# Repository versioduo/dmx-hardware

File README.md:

# dmx-hardware

🚥 MIDI to DMX Bridge

## Board

## Schematic

[PDF](dmx.pdf)

## Bill Of Materials

[Interactive BOM](https://htmlpreview.github.io/?https://github.com/versioduo/dmx-hardware/main/dmx-bom.html)

## Software

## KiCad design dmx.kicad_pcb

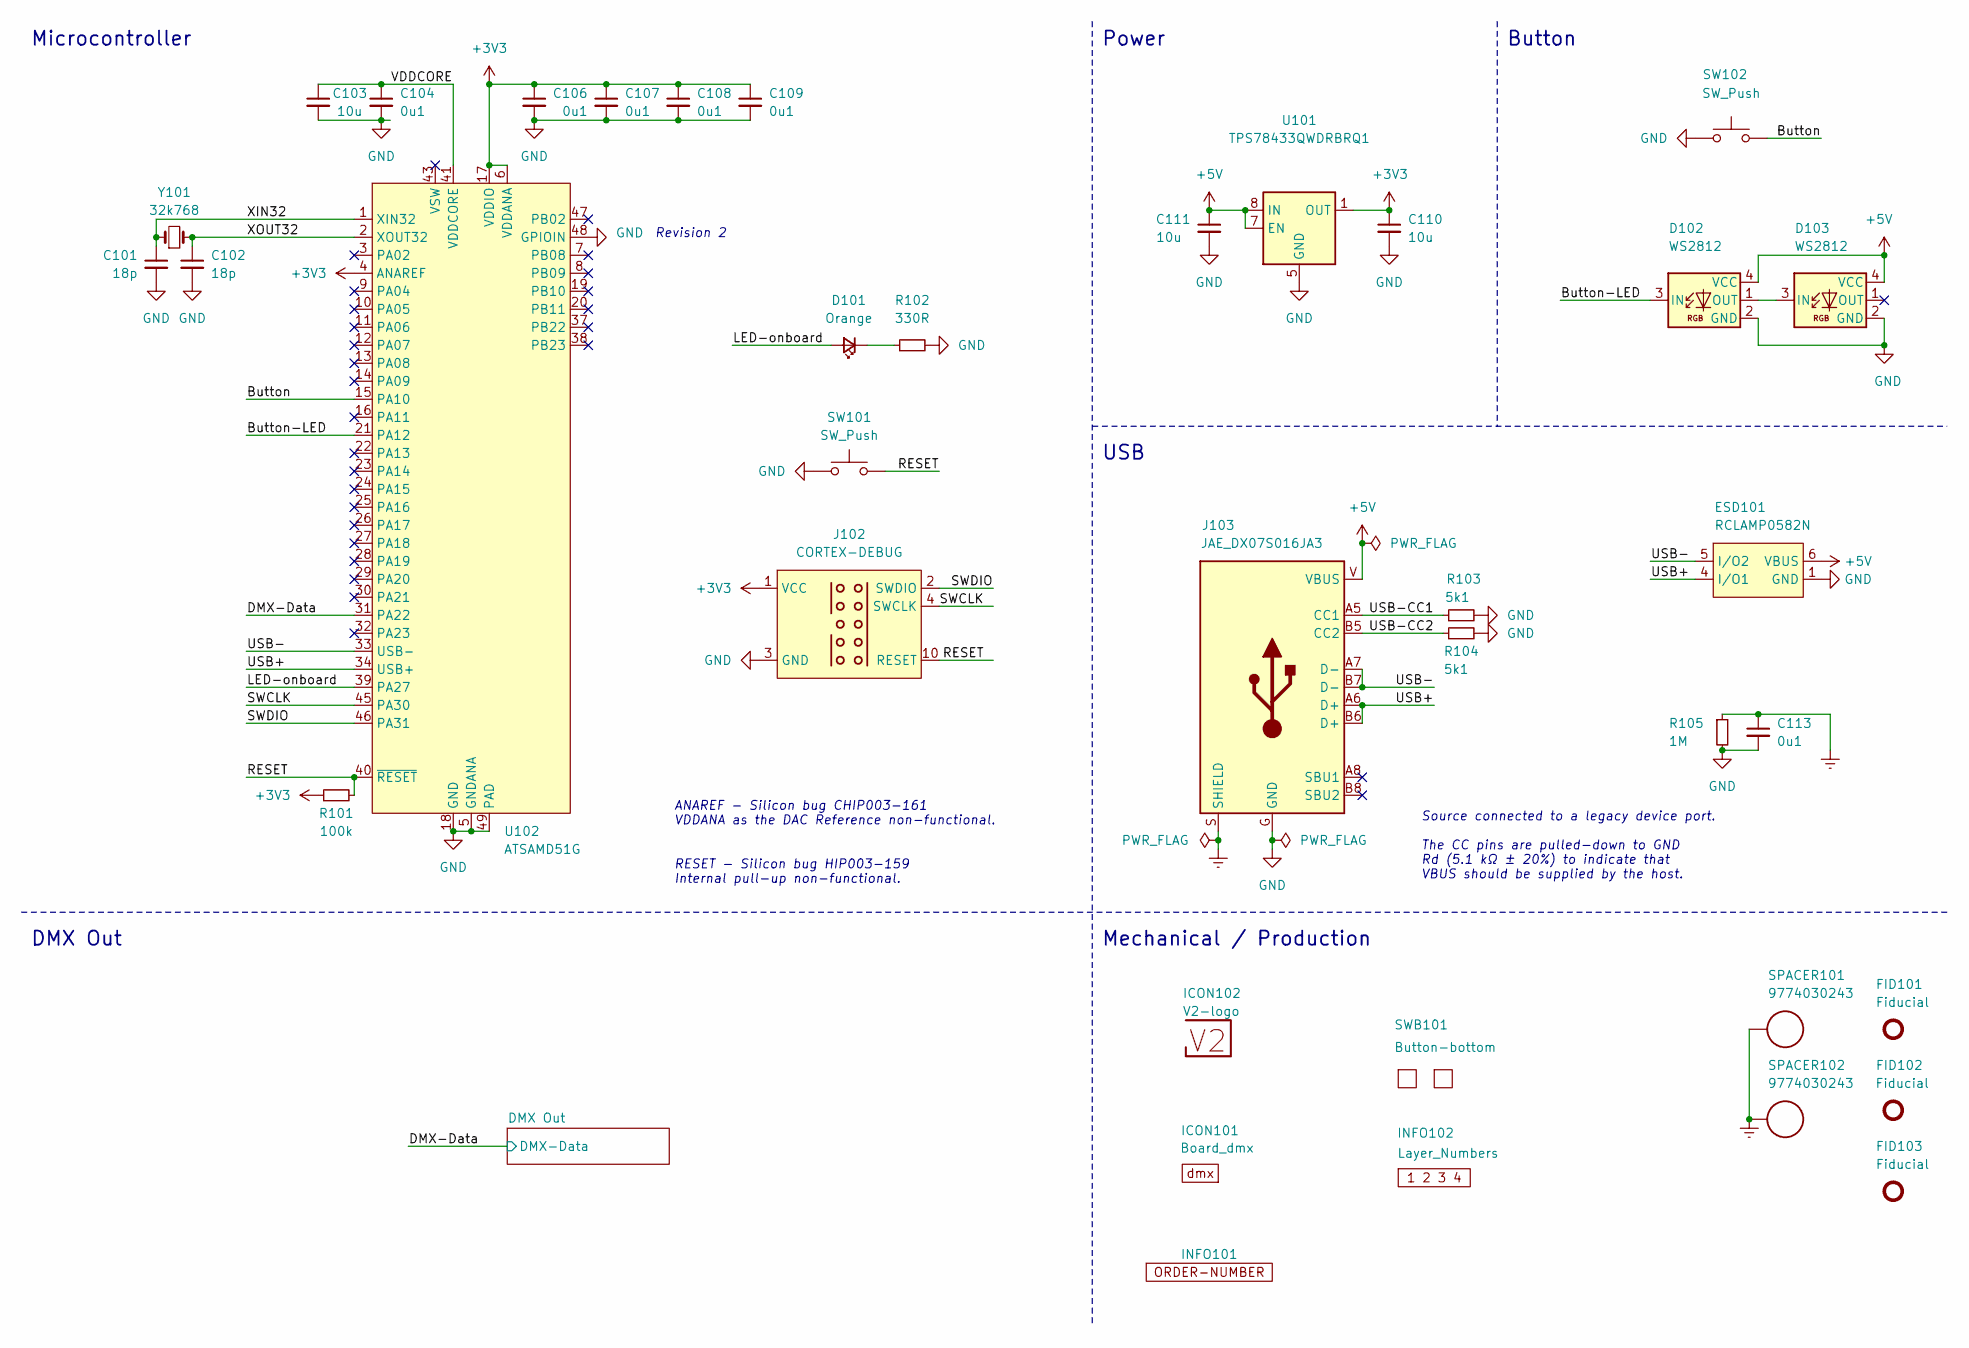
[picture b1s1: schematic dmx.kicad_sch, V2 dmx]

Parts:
C101, C102: 18p; C_0603_1608Metric
C103, C110, C111: 10u; C_0603_1608Metric
C104, C106, C107, C108, C109, C113: 0u1; C_0603_1608Metric
D101: Orange; LED_0603_1608Metric
D102, D103: WS2812; WS2812-2020
ESD101: RCLAMP0582N; SLP1210N6
FID101, FID102, FID103: Fiducial; Fiducial_0.5mm_Mask1mm_Paste
ICON101: Board_dmx; Board_dmx_Small
ICON102: V2-logo; Logo_Small
INFO101: ORDER-NUMBER; Order_Number
INFO102: Layer_Numbers
J102: CORTEX-DEBUG; Cortex_Debug_Pad
J103: JAE_DX07S016JA3
R101: 100k; R_0603_1608Metric
R102: 330R; R_0603_1608Metric
R103, R104: 5k1; R_0603_1608Metric
R105: 1M; R_0603_1608Metric
SPACER101, SPACER102: 9774030243
SW101, SW102: SW_Push; SKSG
SWB101: Button-bottom; PCB_Button-bottom
U101: TPS78433QWDRBRQ1; VSON-8-1_3x3mm_P0.65_EP1.65x2.4mm
U102: ATSAMD51G; QFN-48-1EP_7x7mm_P0.5mm_EP5.45x5.45mm_ThermalVias
Y101: 32k768; Crystal_SMD_3215-2Pin_3.2x1.5mm

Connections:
+3V3: C106.1, C107.1, C108.1, C109.1, C110.1, J102.1 (VCC), R101.1, U101.1 (OUT), U102.4 (ANAREF), U102.6 (VDDANA), U102.17 (VDDIO), U102.36 (VDDIO), U102.44 (VDDIO); also elsewhere on the board
+5V: C111.1, D102.4 (VCC), D103.4 (VCC), ESD101.6 (VBUS), J103.V (VBUS), U101.7 (EN), U101.8 (IN)
/Button: SW102.2, U102.15 (PA10)
/Button-LED: D102.3 (IN), U102.21 (PA12)
/DMX-Data: U102.31 (PA22); also elsewhere on the board
/LED-onboard: D101.2 (A), U102.39 (PA27)
/RESET: J102.10 (RESET), R101.2, SW101.2, U102.40 (~RESET)
/SWCLK: J102.4 (SWCLK), U102.45 (PA30)
/SWDIO: J102.2 (SWDIO), U102.46 (PA31)
/USB+: ESD101.4 (I/O1), J103.A6 (D+), J103.B6 (D+), U102.34 (USB+)
/USB-: ESD101.5 (I/O2), J103.A7 (D-), J103.B7 (D-), U102.33 (USB-)
/USB-CC1: J103.A5 (CC1), R103.1
/USB-CC2: J103.B5 (CC2), R104.1
/VDDCORE: C103.1, C104.1, U102.41 (VDDCORE)
/XIN32: C101.1, U102.1 (XIN32), Y101.1
/XOUT32: C102.1, U102.2 (XOUT32), Y101.2
Earth: C113.1, J103.S (SHIELD), R105.1, SPACER101.1, SPACER102.1
GND: C101.2, C102.2, C103.2, C104.2, C106.2, C107.2, C108.2, C109.2, C110.2, C111.2, C113.2, D102.2 (GND), D103.2 (GND), ESD101.1 (GND), J102.3 (GND), J102.5 (GND), J103.G (GND), R102.2, R103.2, R104.2, R105.2, SW101.1, SW102.1, U101.5 (GND), U101.9 (GND), U102.5 (GNDANA), U102.18 (GND), U102.35 (GND), U102.42 (GND), U102.48 (GPIOIN), U102.49 (PAD); also elsewhere on the board
unnamed: D101.1 (K), R102.1
unnamed: D102.1 (OUT), D103.3 (IN)

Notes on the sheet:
﻿ANAREF - Silicon bug CHIP003-161 VDDANA as the DAC Reference non-functional.
RESET - ﻿Silicon bug HIP003-159 Internal pull-up non-functional.
﻿Source connected to a legacy device port. The CC pins are pulled-down to GND Rd (5.1 kΩ ± 20%) to indicate that VBUS should be supplied by the host.
Button
Revision 2
Mechanical / Production
Power
Microcontroller
USB
DMX Out

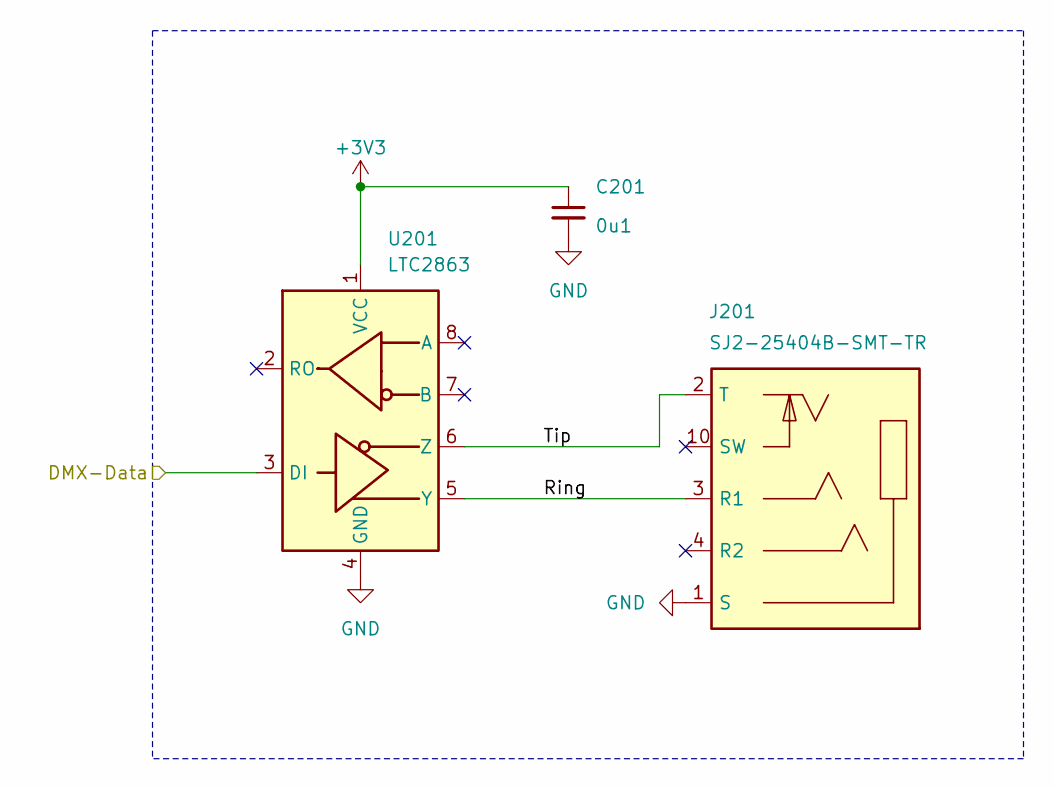
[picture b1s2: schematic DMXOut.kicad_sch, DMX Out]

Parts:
C201: 0u1; C_0603_1608Metric
J201: SJ2-25404B-SMT-TR; CUI_SJ2-25404B-SMT-TR
U201: LTC2863; DFN-8-1EP_3x3mm_P0.5mm_EP1.65x2.38mm

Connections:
+3V3: C201.1, U201.1 (VCC); also elsewhere on the board
/DMX Out/Ring: J201.3 (R1), U201.5 (Y)
/DMX Out/Tip: J201.2 (T), U201.6 (Z)
/DMX-Data: U201.3 (DI); also elsewhere on the board
GND: C201.2, J201.1 (S), U201.4 (GND), U201.9 (GND); also elsewhere on the board

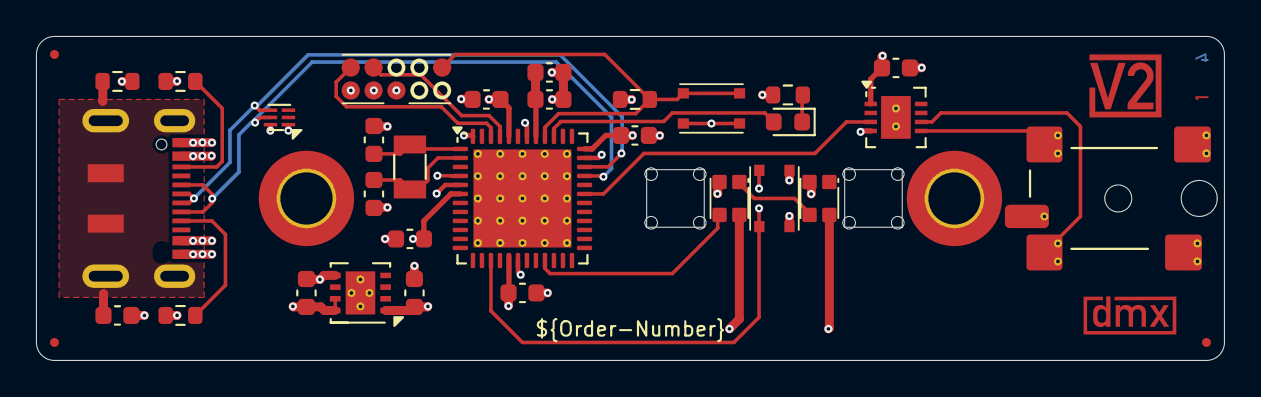
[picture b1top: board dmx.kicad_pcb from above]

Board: 4 copper layers, 66.0 x 18.0 mm, 40 parts (0 on the bottom side), 22 nets.

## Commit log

2023-01-05 Import
2023-07-01 Refresh
2024-03-28 Update to Kicad 8
2024-07-17 Update TRS socket
